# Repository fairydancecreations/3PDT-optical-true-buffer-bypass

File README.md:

# 3PDT-optical-true-bypass
3PDT optical true bypass PCB , eagle file and gerbers
Ignore the 4pdt name files. these are an older name and file. they are working and slightly bigger pcb for the buffered version
smd parts are voltage smoothing and current liminter for the LED. 
the main current limiter is the trim pot for adjusting the brightness
2 LED footprints for top and side mounted options. you can use both. but why?
optocoupler is a TLP222A or TLP222G. cheap low cost ones will work and most have the same pinout.

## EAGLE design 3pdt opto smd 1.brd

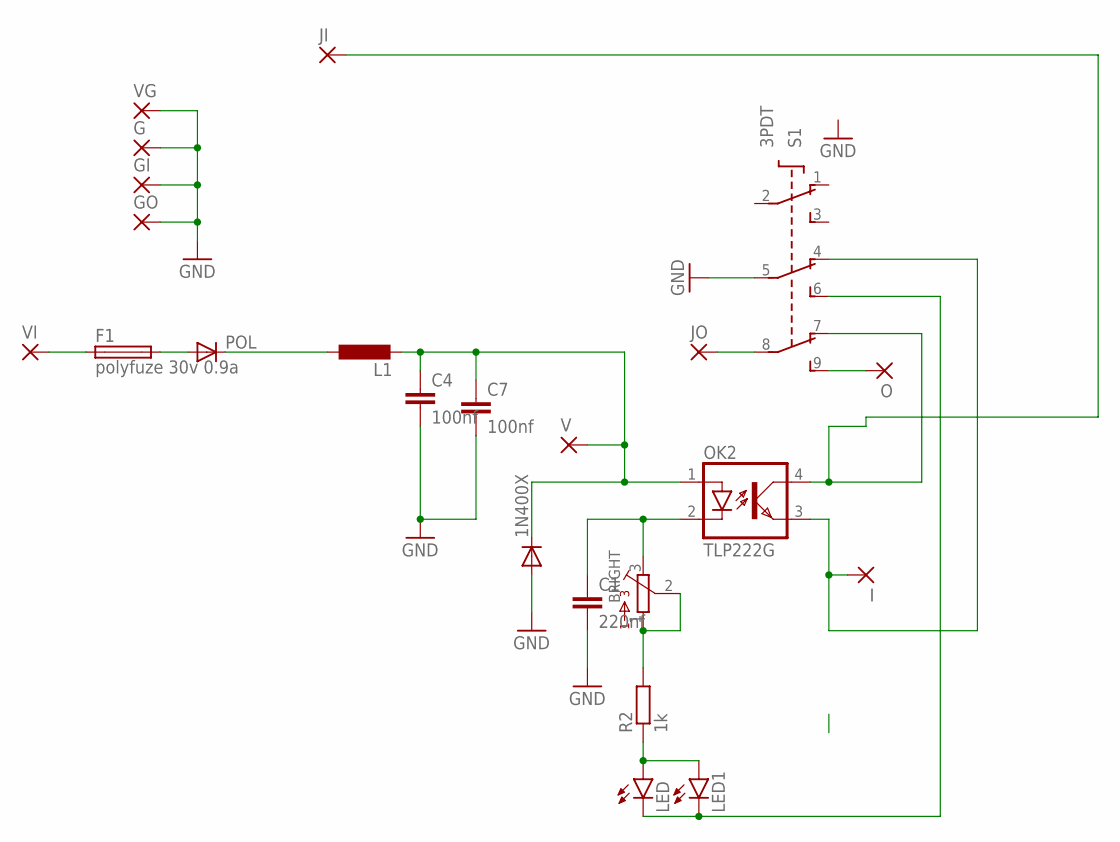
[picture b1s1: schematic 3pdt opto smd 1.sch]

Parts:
1N400X: SMALL_DIODEDO35-7; DO35-7
BRIGHT: BOURNS_3362P_TRIMMERP; BOURNS_3362P_TRIMMER
C1: 220nf; C0805K
C4, C7: 100nf; C0805K
F1: polyfuze 30v 0.9a; 19559
G: 2,15/1,0
GI: 2,15/1,0
GO: 2,15/1,0
I: 2,15/1,0
JI: 2,15/1,0
JO: 2,15/1,0
L1: L-EU0204/7; 0204/7
LED, LED1: LED3MM
O: 2,15/1,0
OK2: TLP222G; DIL04
POL: SMALL_DIODEDO35-7; DO35-7
R2: 1k; M1206
S1: 3PDT
V: 2,15/1,0
VG: 2,15/1,0
VI: 2,15/1,0

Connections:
GND: 1N400X.A, C1.2, G.1, GI.1, GO.1, S1.5 (P2), VG.1
unnamed: JO.1, S1.8 (P3)
unnamed: BRIGHT.3, C1.1, OK2.2 (C)
unnamed: LED.K (C), LED1.K (C), S1.6 (S2)
unnamed: LED.A, LED1.A, R2.1
unnamed: F1.1, VI.1
unnamed: O.1, S1.9 (S3)
unnamed: L1.1, POL.C
unnamed: I.1, OK2.3 (EMIT), S1.4 (O2)
unnamed: C4.2, C7.2
unnamed: BRIGHT.1, BRIGHT.2, R2.2
unnamed: F1.2, POL.A
unnamed: JI.1, OK2.4 (COL), S1.7 (O3)
VCC1: 1N400X.C, C4.1, C7.1, L1.2, OK2.1 (A), V.1

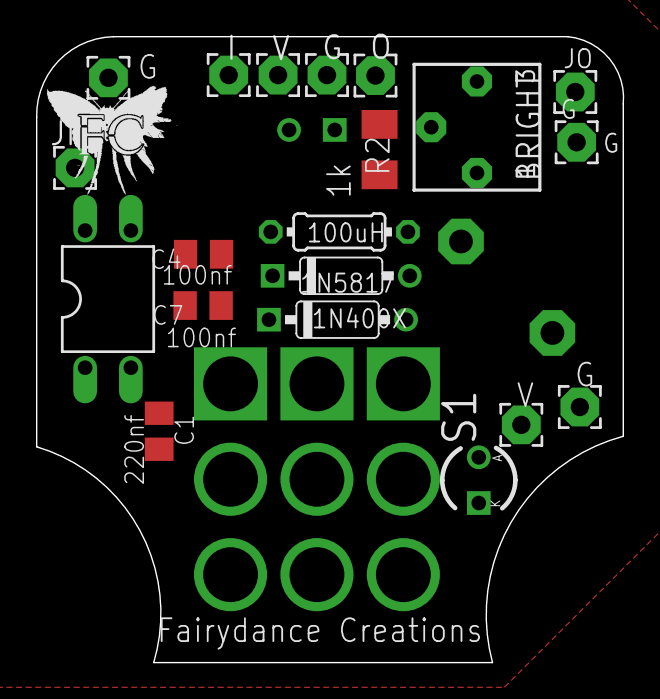
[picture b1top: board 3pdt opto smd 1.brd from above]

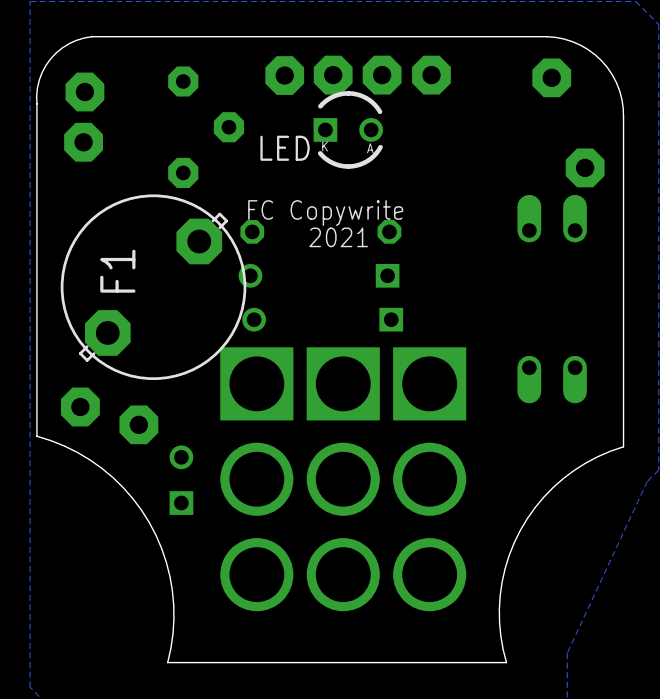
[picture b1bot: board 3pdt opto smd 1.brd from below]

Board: 2 copper layers, 32.6 x 34.8 mm, 23 parts (2 on the bottom side), 14 nets.
